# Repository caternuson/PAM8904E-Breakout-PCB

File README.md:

# PAM8904E-Breakout-PCB
KiCAD PCB files for PAM8904E breakout

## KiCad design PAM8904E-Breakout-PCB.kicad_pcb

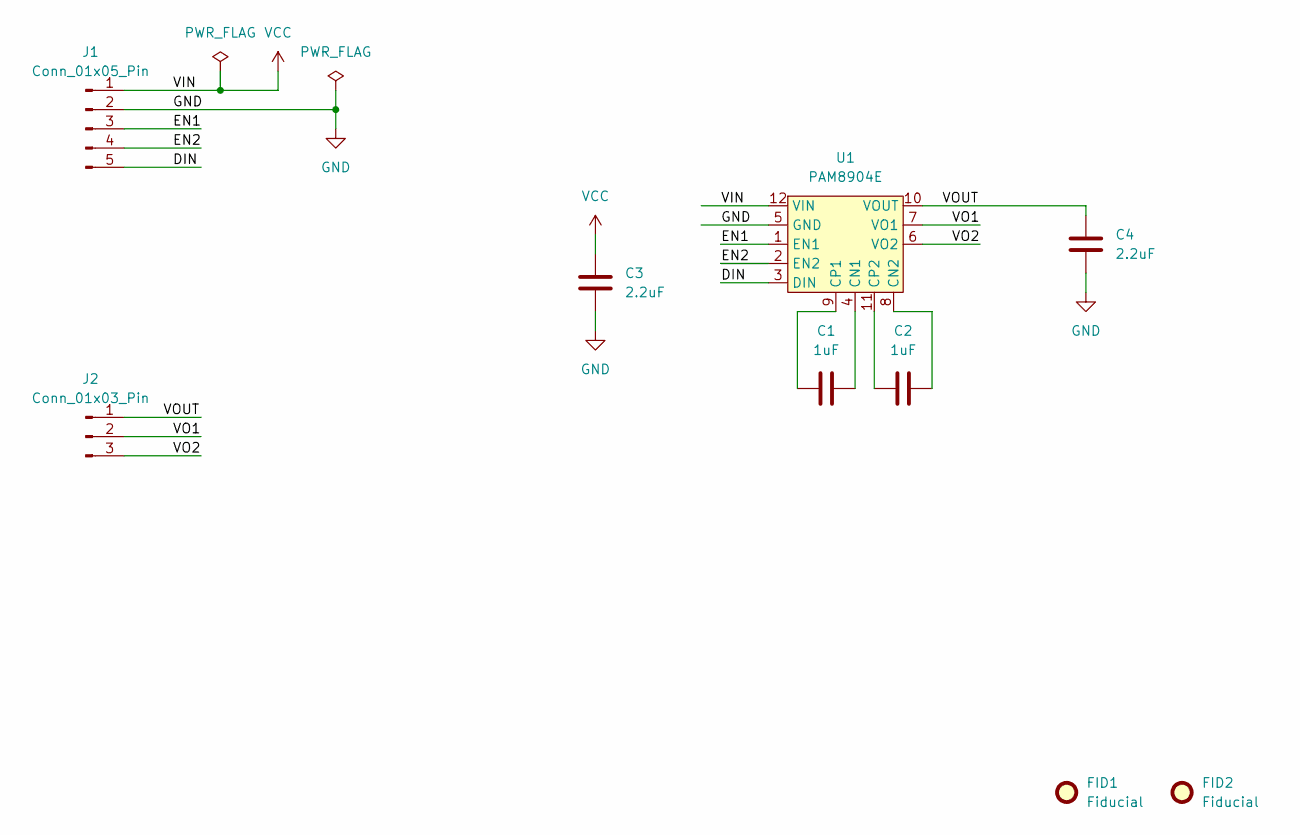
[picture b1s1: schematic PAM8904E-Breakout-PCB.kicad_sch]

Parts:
C1, C2: 1uF; C_0603_1608Metric; LCSC C77049
C3, C4: 2.2uF; C_0603_1608Metric; LCSC C2835569
FID1, FID2: Fiducial; Fiducial_0.5mm_Mask1mm
J1: Conn_01x05_Pin; PinHeader_1x05_P2.54mm_Vertical
J2: Conn_01x03_Pin; PinHeader_1x03_P2.54mm_Vertical
U1: PAM8904E; QFN-12_EP_2.05x2.05_Pitch0.4mm; LCSC C510550

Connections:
/DIN: J1.5, U1.3 (DIN)
/EN1: J1.3, U1.1 (EN1)
/EN2: J1.4, U1.2 (EN2)
/VO1: J2.2, U1.7 (VO1)
/VO2: J2.3, U1.6 (VO2)
/VOUT: C4.1, J2.1, U1.10 (VOUT)
GND: C3.2, C4.2, J1.2, U1.5 (GND)
unnamed: C1.2, U1.4 (CN1)
unnamed: C2.2, U1.8 (CN2)
unnamed: C1.1, U1.9 (CP1)
unnamed: C2.1, U1.11 (CP2)
VCC: C3.1, J1.1, U1.12 (VIN)

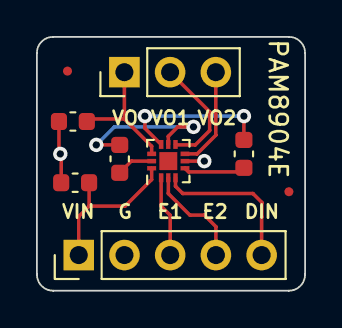
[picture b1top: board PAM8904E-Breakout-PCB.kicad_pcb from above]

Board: 2 copper layers, 14.9 x 14.1 mm, 9 parts (0 on the bottom side), 12 nets.

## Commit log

2023-07-12 add files
2023-07-24 board as ordered
